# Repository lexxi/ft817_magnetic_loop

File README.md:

# ft817_magnetic_loop
This is a fork from --> https://github.com/8cH9azbsFifZ/arduino_ft817/tree/master/examples/ft_817_automatic_loop

The code is based on Alain De Carolis, WW3WW, FT-817 Automatic Loop Tuner (https://code.google.com/p/ft-817-automatic-loop/)
   
This progam uses a modified version of the qrptracker library
written by Bruce Gordon Robertson, VE9QRP
    
released under the GPL V3 license
    
I have added a 16x2 LCD display with some infos of the rig an the possibility to work with a digital interface and 
this tuner.

Board by OE8WUR

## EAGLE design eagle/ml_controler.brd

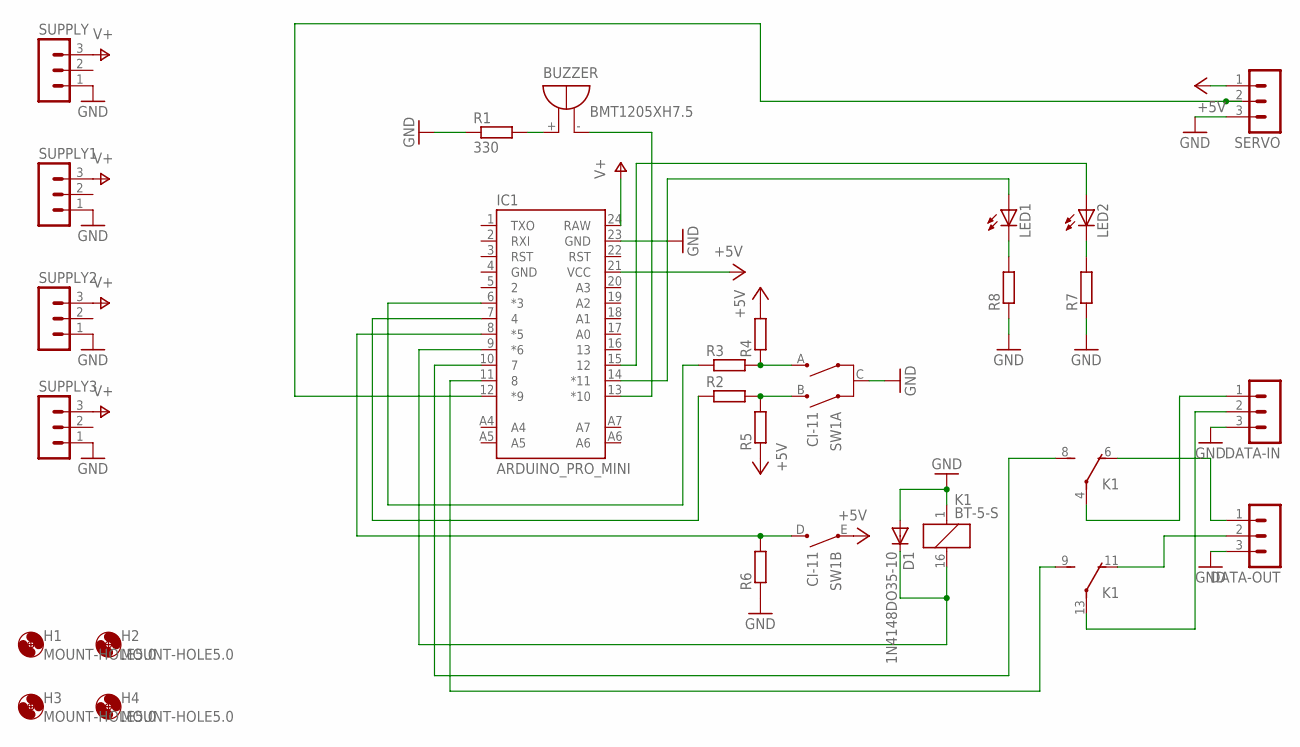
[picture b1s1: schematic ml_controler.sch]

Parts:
BUZZER: BMT1205XH7.5
D1: 1N4148DO35-10; DO35-10
DATA-IN: MA03-1
DATA-OUT: MA03-1
H1, H2, H3, H4: MOUNT-HOLE5.0; 5,0
IC1: ARDUINO_PRO_MINI
K1: BT-5-S; BT-XX-S
LED1, LED2: LED5MM
R1: 330; 0207/12
R2, R3, R4, R5, R6, R7, R8: R-EU_0207/12; 0207/12
SERVO: MA03-1
SUPPLY, SUPPLY1, SUPPLY2, SUPPLY3: MA03-1
SW1: CI-11

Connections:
+5V: IC1.21 (VCC), R4.2, R5.1, SERVO.1, SW1.E
GND: D1.A, DATA-IN.3, DATA-OUT.3, IC1.23 (GND), K1.1, R1.1, R6.1, R7.1, R8.1, SERVO.3, SUPPLY.1, SUPPLY1.1, SUPPLY2.1, SUPPLY3.1, SW1.C
unnamed: BUZZER.-, IC1.13 (*10)
unnamed: R3.2, R4.1, SW1.A
unnamed: R2.2, R5.2, SW1.B
unnamed: IC1.6 (*3), R3.1
unnamed: IC1.7 (4), R2.1
unnamed: IC1.8 (*5), R6.2, SW1.D
unnamed: IC1.12 (*9), SERVO.2
unnamed: LED2.K (C), R7.2
unnamed: LED1.K (C), R8.2
unnamed: IC1.14 (*11), LED1.A
unnamed: IC1.15 (12), LED2.A
unnamed: D1.C, IC1.9 (*6), K1.16 (2)
unnamed: DATA-IN.1, K1.4
unnamed: DATA-IN.2, K1.13
unnamed: DATA-OUT.1, K1.6 (O)
unnamed: DATA-OUT.2, K1.11 (O)
unnamed: IC1.10 (7), K1.8 (S)
unnamed: IC1.11 (8), K1.9 (S)
unnamed: BUZZER.+, R1.2
V+: IC1.24 (RAW), SUPPLY.3, SUPPLY1.3, SUPPLY2.3, SUPPLY3.3

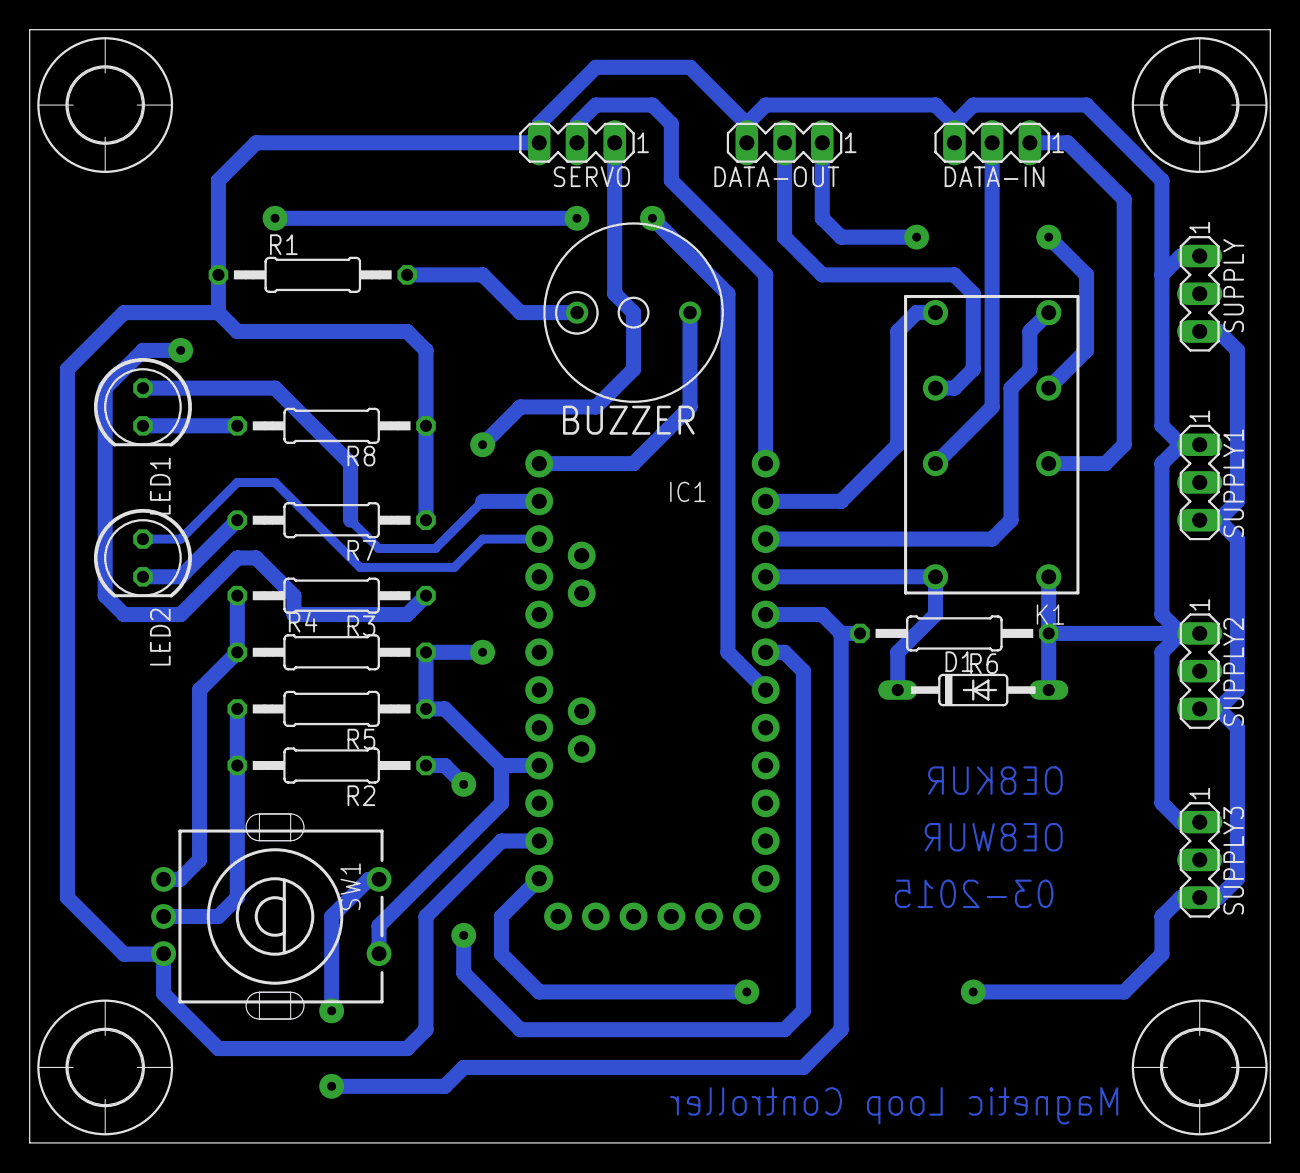
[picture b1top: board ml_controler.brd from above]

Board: 2 copper layers, 83.5 x 74.9 mm, 26 parts (0 on the bottom side), 22 nets.

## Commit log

2015-03-09 all changes since first checkout just in one stepp
2015-03-28 first test commit
2015-03-28 added board layout and schematic
2015-03-28 some typos..
2015-03-28 small corrections

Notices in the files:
parts and their libraries:
SparkFun-Boards: Licensing: Creative Commons ShareAlike 4.0 International - https://creativecommons.org/licenses/by-sa/4.0
